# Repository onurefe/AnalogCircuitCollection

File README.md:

# AnalogCircuitCollection
Collection of analog circuits which can be useful in various fields.

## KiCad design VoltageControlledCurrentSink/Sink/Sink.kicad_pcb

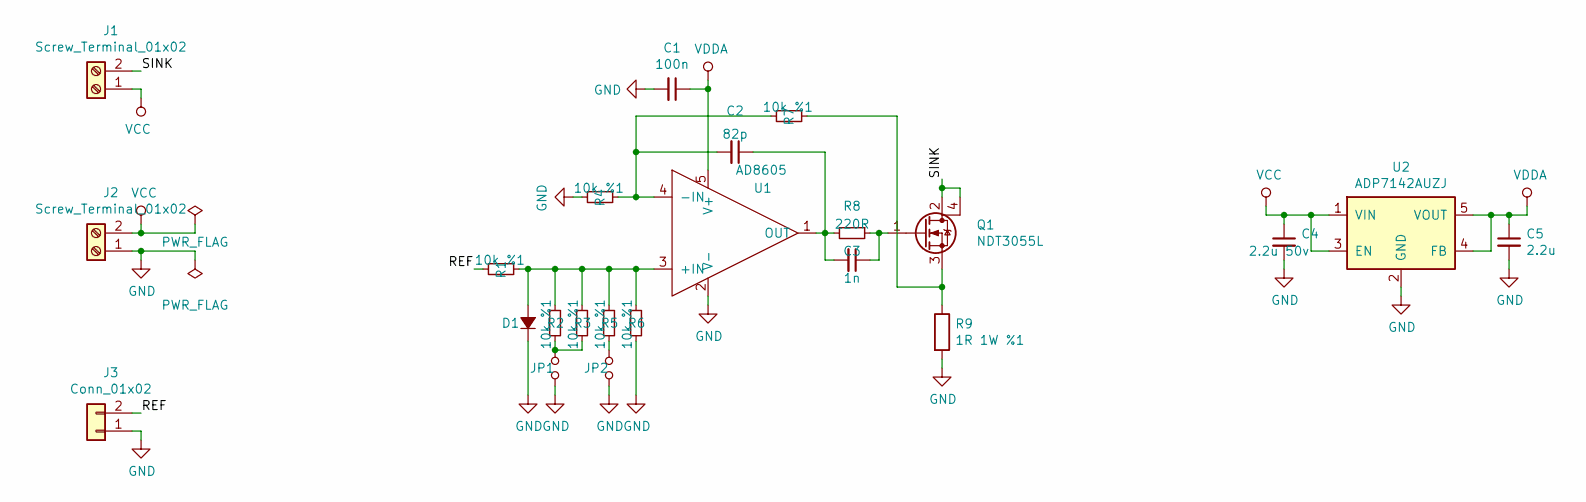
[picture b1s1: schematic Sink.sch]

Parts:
C1: 100n; C_0805_2012Metric
C2: 82p; C_0805_2012Metric
C3: 1n; C_0805_2012Metric
C4: 2.2u 50v; C_0805_2012Metric
C5: 2.2u; C_0805_2012Metric
D1: 1N4148; D_SOD-323
J1, J2: Screw_Terminal_01x02; TerminalBlock_bornier-2_P5.08mm
J3: Conn_01x02; PinHeader_1x02_P2.54mm_Vertical
JP1, JP2: Jumper_NO_Small; PinHeader_1x02_P2.54mm_Vertical
Q1: NDT3055L; SOT-223
R1, R2, R3, R4, R5, R6, R7: 10k %1; R_0805_2012Metric
R8: 220R; R_0805_2012Metric
R9: 1R 1W %1; R_2512_6332Metric
U1: AD8605; SOT-23-5
U2: ADP7142AUZJ; TSOT-23-5

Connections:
/REF: J3.2, R1.2
/SINK: J1.2, Q1.2 (D), Q1.4 (D)
GND: C1.2, C4.2, C5.2, D1.1 (K), J2.1, J3.1, JP1.1, JP2.1, R4.2, R6.2, R9.2, U1.2 (V-), U2.2 (GND)
unnamed: C2.1, C3.2, R8.2, U1.1 (OUT)
unnamed: C2.2, R4.1, R7.2, U1.4 (-IN)
unnamed: C3.1, Q1.1 (G), R8.1
unnamed: D1.2 (A), R1.1, R2.1, R3.1, R5.1, R6.1, U1.3 (+IN)
unnamed: JP1.2, R2.2, R3.2
unnamed: JP2.2, R5.2
unnamed: Q1.3 (S), R7.1, R9.1
VCC: C4.1, J1.1, J2.2, U2.1 (VIN), U2.3 (EN)
VDDA: C1.1, C5.1, U1.5 (V+), U2.4 (FB), U2.5 (VOUT)

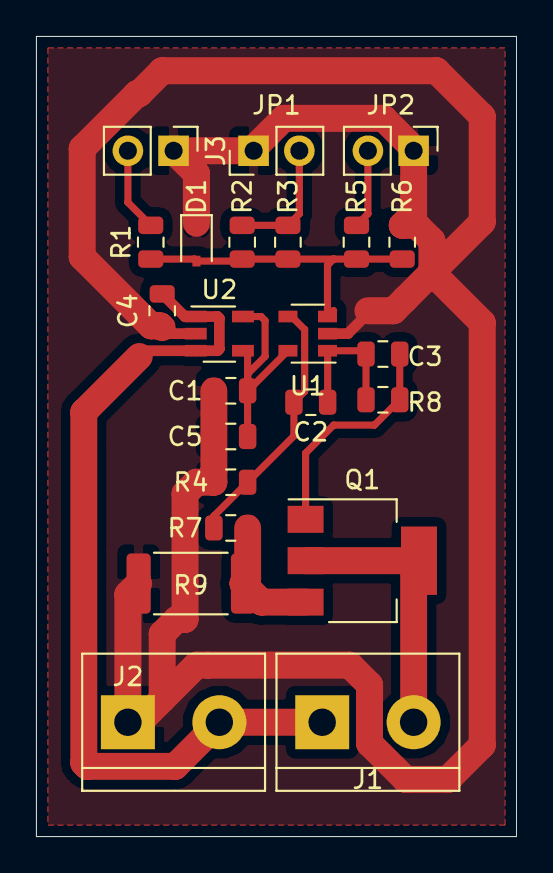
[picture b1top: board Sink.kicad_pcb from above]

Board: 2 copper layers, 26.7 x 44.5 mm, 23 parts (0 on the bottom side), 12 nets.

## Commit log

2019-01-07 Schematic and PCB completed.
2019-01-07 BOM List v1.0 and Gerbers for Home-Brew circuit
2020-09-02 Regular commit.
